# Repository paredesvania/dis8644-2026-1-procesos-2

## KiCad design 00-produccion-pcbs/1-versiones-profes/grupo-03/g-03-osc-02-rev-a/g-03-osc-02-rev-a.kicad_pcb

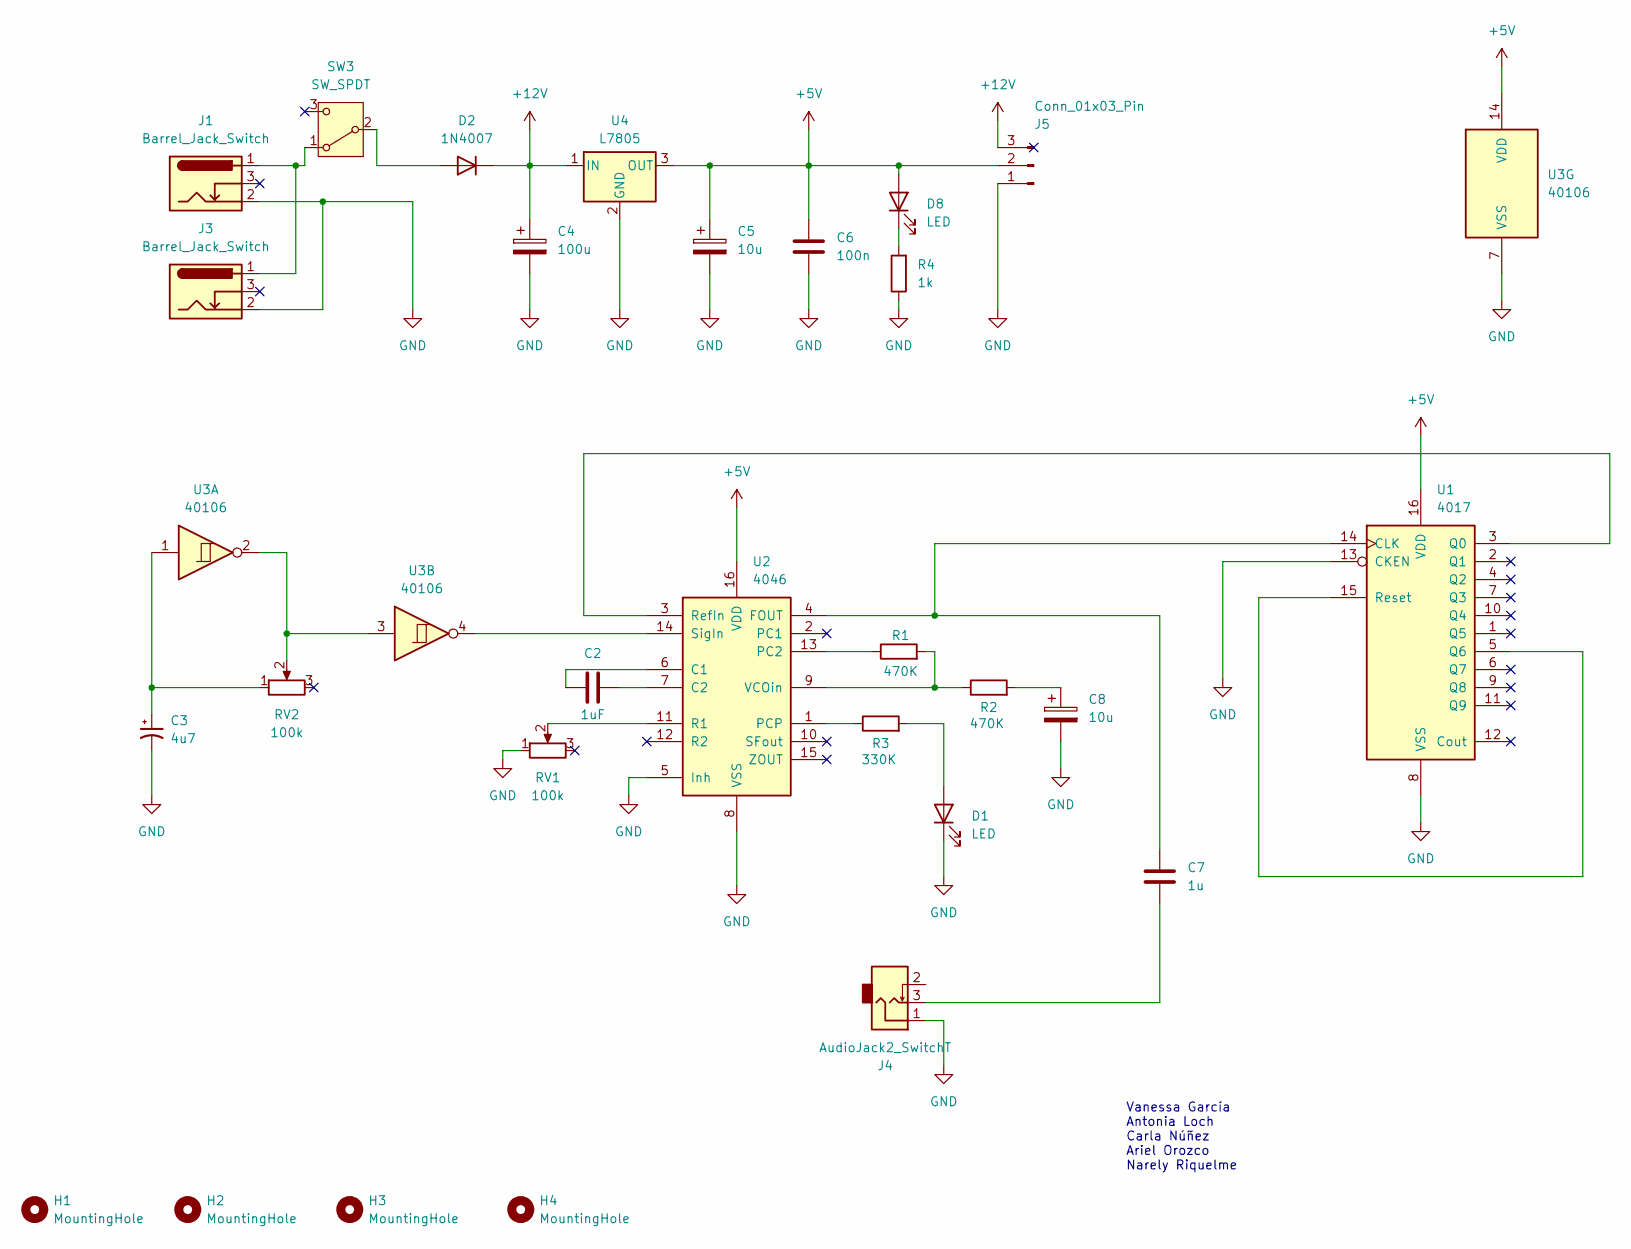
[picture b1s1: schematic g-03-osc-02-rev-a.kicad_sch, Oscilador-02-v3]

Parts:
C2: 1uF; CP_Radial_D5.0mm_P2.00mm
C3: 4u7; CP_Radial_D5.0mm_P2.00mm
C4: 100u; CP_Radial_D8.0mm_P3.80mm
C5, C8: 10u; CP_Radial_D4.0mm_P2.00mm
C6: 100n; C_Disc_D5.0mm_W2.5mm_P2.50mm
C7: 1u; C_Disc_D5.0mm_W2.5mm_P2.50mm
D1, D8: LED; LED_D5.0mm
D2: 1N4007; D_DO-41_SOD81_P10.16mm_Horizontal
H1, H2, H3, H4: MountingHole; MountingHole_3.2mm_M3
J1, J3: Barrel_Jack_Switch; BarrelJack_Horizontal
J4: AudioJack2_SwitchT; PJ301M-12
J5: Conn_01x03_Pin; PinSocket_1x03_P2.54mm_Vertical
R1, R2: 470K; R_Axial_DIN0207_L6.3mm_D2.5mm_P10.16mm_Horizontal
R3: 330K; R_Axial_DIN0207_L6.3mm_D2.5mm_P10.16mm_Horizontal
R4: 1k; R_Axial_DIN0207_L6.3mm_D2.5mm_P10.16mm_Horizontal
RV1, RV2: 100k; Potentiometer_Alps_RK163_Single_Horizontal
SW3: SW_SPDT; spdt_ssd12d00g3
U1: 4017; DIP-16_W7.62mm_LongPads
U2: 4046; DIP-16_W7.62mm_LongPads
U3: 40106; DIP-14_W7.62mm_LongPads
U4: L7805; TO-220-3_Horizontal_TabDown

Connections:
+5V: C5.1, C6.1, D8.2 (A), J5.2, U1.16 (VDD), U2.16 (VDD), U3.14 (VDD), U4.3 (OUT)
+12V: C4.1, D2.1 (K), J5.3, U4.1 (IN)
GND: C3.2, C4.2, C5.2, C6.2, C8.2, D1.1 (K), J1.2, J3.2, J4.1, J5.1, R4.1, RV1.1, U1.8 (VSS), U1.13 (CKEN), U2.5 (Inh), U2.8 (VSS), U3.7 (VSS), U4.2 (GND)
unnamed: C3.1, RV2.1, U3.1
unnamed: C7.2, J4.3
unnamed: C8.1, R2.2
unnamed: D1.2 (A), R3.2
unnamed: D2.2 (A), SW3.2 (B)
unnamed: D8.1 (K), R4.2
unnamed: RV2.2, U3.2, U3.3
unnamed: J1.1, J3.1, SW3.1 (A)
unnamed: C7.1, U1.14 (CLK), U2.4 (FOUT)
unnamed: U1.3 (Q0), U2.3 (RefIn)
unnamed: U1.5 (Q6), U1.15 (Reset)
unnamed: C2.1, U2.6 (C1)
unnamed: C2.2, U2.7 (C2)
unnamed: R1.1, U2.13 (PC2)
unnamed: R3.1, U2.1 (PCP)
unnamed: RV1.2, U2.11 (R1)
unnamed: U2.14 (SigIn), U3.4
unnamed: R1.2, R2.1, U2.9 (VCOin)

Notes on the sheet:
Vanessa García Antonia Loch Carla Núñez Ariel Orozco Narely Riquelme

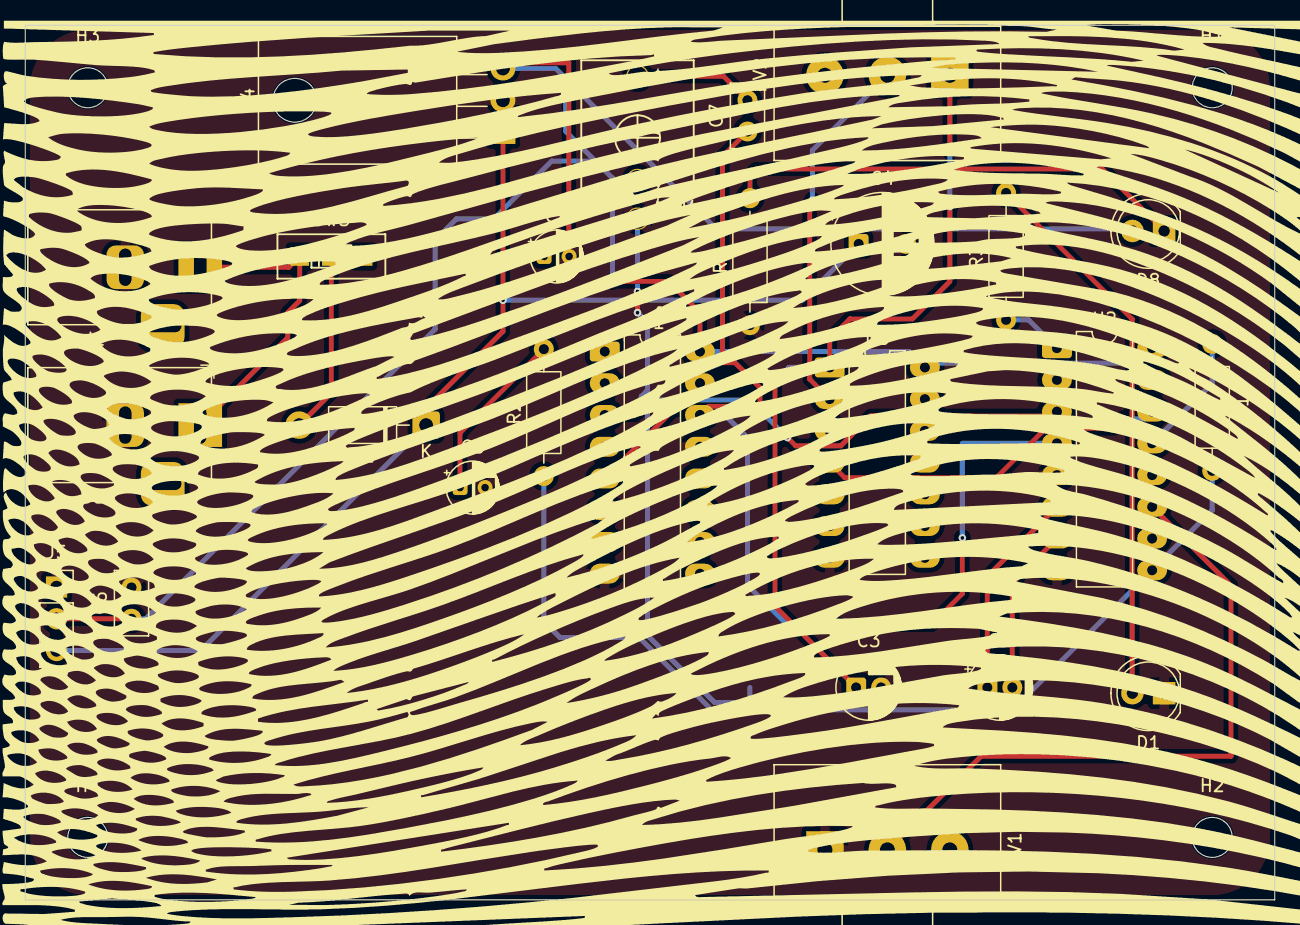
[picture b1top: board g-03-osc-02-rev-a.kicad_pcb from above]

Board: 2 copper layers, 100.0 x 70.0 mm, 29 parts (0 on the bottom side), 21 nets.

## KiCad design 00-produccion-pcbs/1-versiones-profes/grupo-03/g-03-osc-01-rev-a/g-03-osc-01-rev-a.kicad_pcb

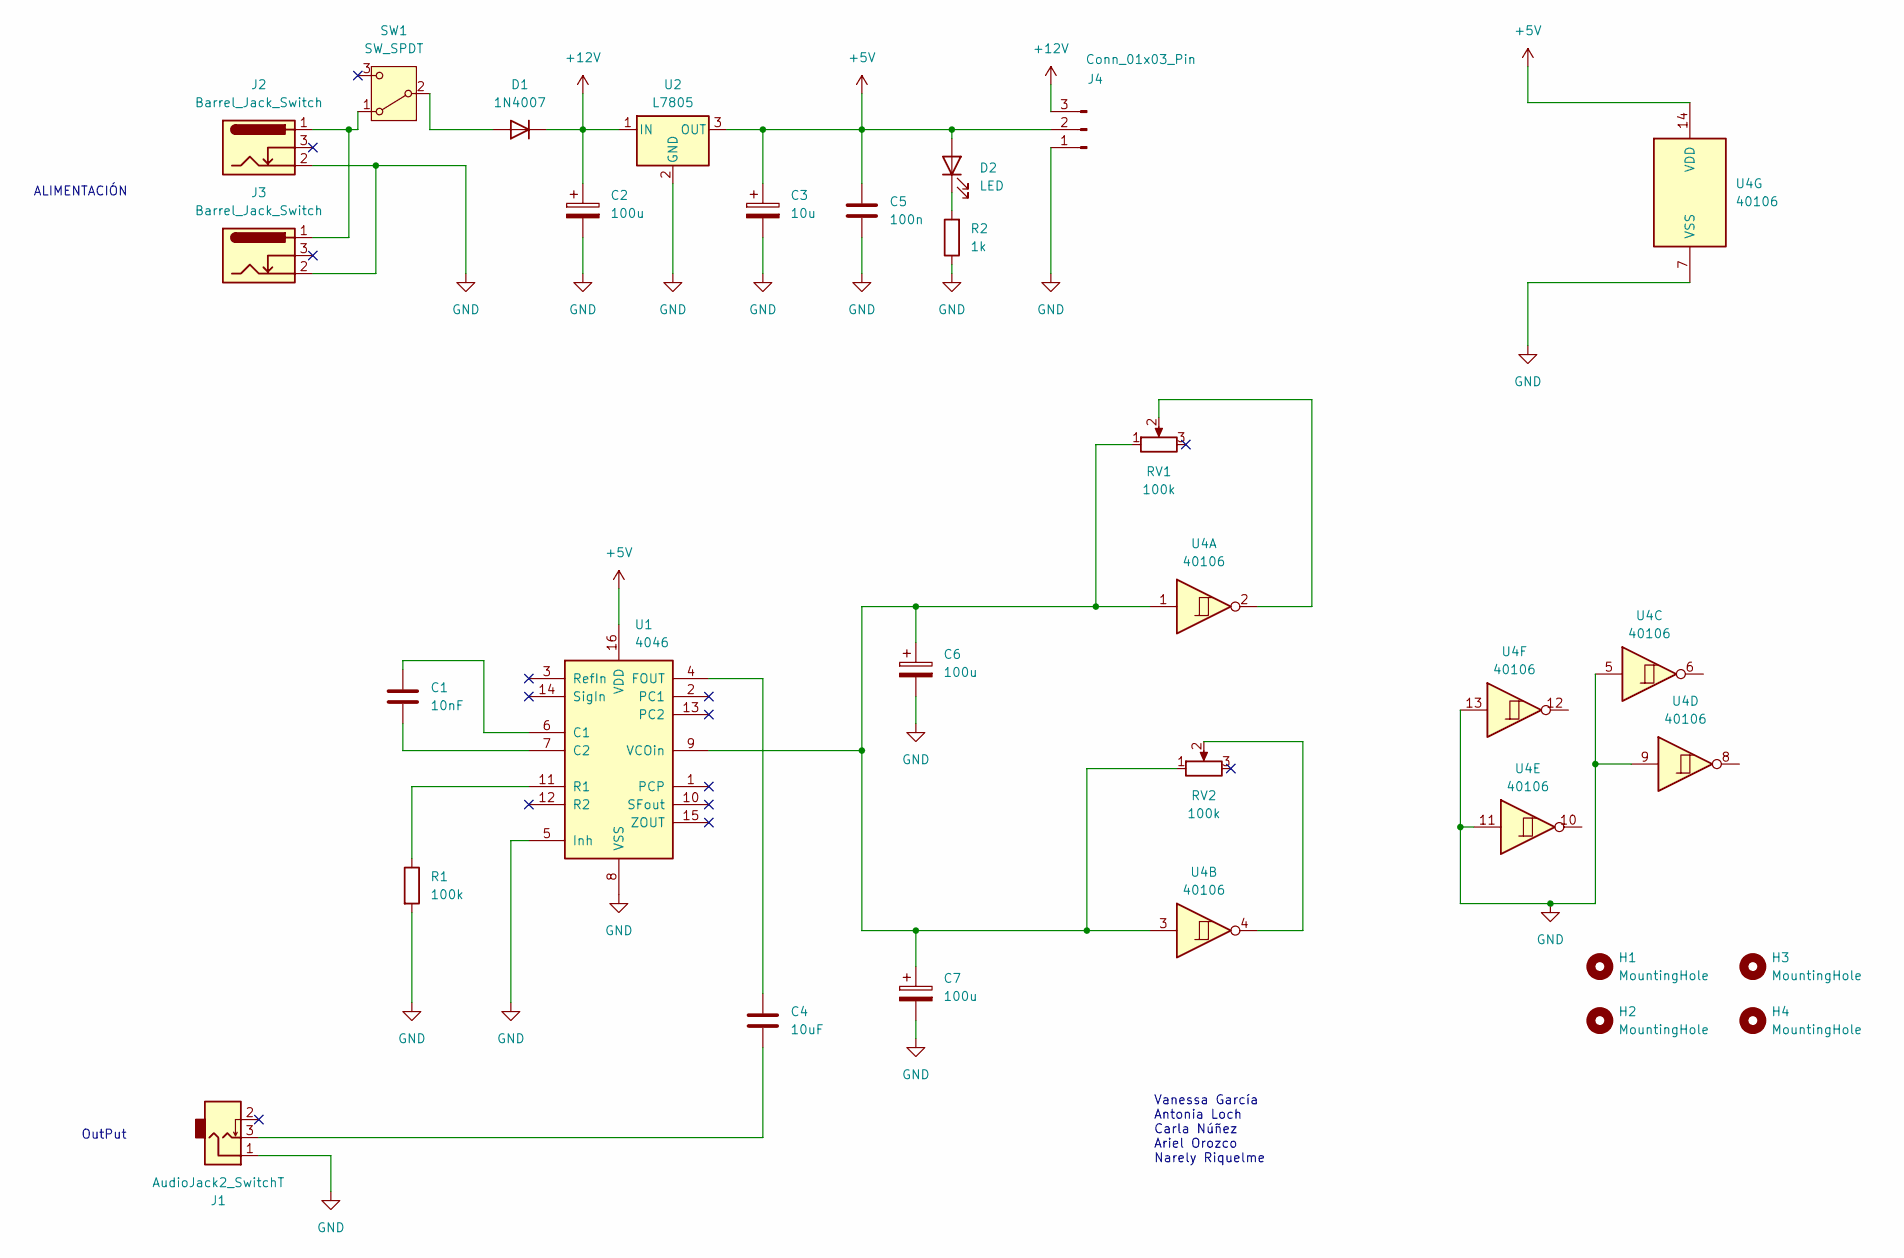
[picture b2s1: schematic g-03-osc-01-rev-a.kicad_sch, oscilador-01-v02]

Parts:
C1: 10nF; C_Disc_D3.8mm_W2.6mm_P2.50mm
C2, C6, C7: 100u; CP_Radial_D8.0mm_P3.80mm
C3: 10u; CP_Radial_D4.0mm_P2.00mm
C4: 10uF; CP_Radial_D5.0mm_P2.00mm
C5: 100n; C_Disc_D5.0mm_W2.5mm_P2.50mm
D1: 1N4007; D_DO-41_SOD81_P10.16mm_Horizontal
D2: LED; LED_D5.0mm
H1, H2, H3, H4: MountingHole; MountingHole_3.2mm_M3
J1: AudioJack2_SwitchT; PJ301M-12
J2, J3: Barrel_Jack_Switch; BarrelJack_Horizontal
J4: Conn_01x03_Pin; PinSocket_1x03_P2.54mm_Vertical
R1: 100k; R_Axial_DIN0207_L6.3mm_D2.5mm_P10.16mm_Horizontal
R2: 1k; R_Axial_DIN0207_L6.3mm_D2.5mm_P10.16mm_Horizontal
RV1, RV2: 100k; Potentiometer_Alps_RK163_Single_Horizontal
SW1: SW_SPDT; spdt_ssd12d00g3
U1: 4046; DIP-16_W7.62mm_LongPads
U2: L7805; TO-220-3_Horizontal_TabDown
U4: 40106

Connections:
+5V: C3.1, C5.1, D2.2 (A), J4.2, U1.16 (VDD), U2.3 (OUT), U4.14 (VDD)
+12V: C2.1, D1.1 (K), J4.3, U2.1 (IN)
GND: C2.2, C3.2, C5.2, C6.2, C7.2, J1.1, J2.2, J3.2, J4.1, R1.2, R2.1, U1.5 (Inh), U1.8 (VSS), U2.2 (GND), U4.5, U4.7 (VSS), U4.9, U4.11, U4.13
unnamed: C4.2, J1.3
unnamed: D1.2 (A), SW1.2 (B)
unnamed: D2.1 (K), R2.2
unnamed: RV1.2, U4.2
unnamed: RV2.2, U4.4
unnamed: J2.1, J3.1, SW1.1 (A)
unnamed: C1.2, U1.6 (C1)
unnamed: C1.1, U1.7 (C2)
unnamed: C4.1, U1.4 (FOUT)
unnamed: R1.1, U1.11 (R1)
unnamed: C6.1, C7.1, RV1.1, RV2.1, U1.9 (VCOin), U4.1, U4.3

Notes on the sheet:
ALIMENTACIÓN
OutPut
Vanessa García Antonia Loch Carla Núñez Ariel Orozco Narely Riquelme

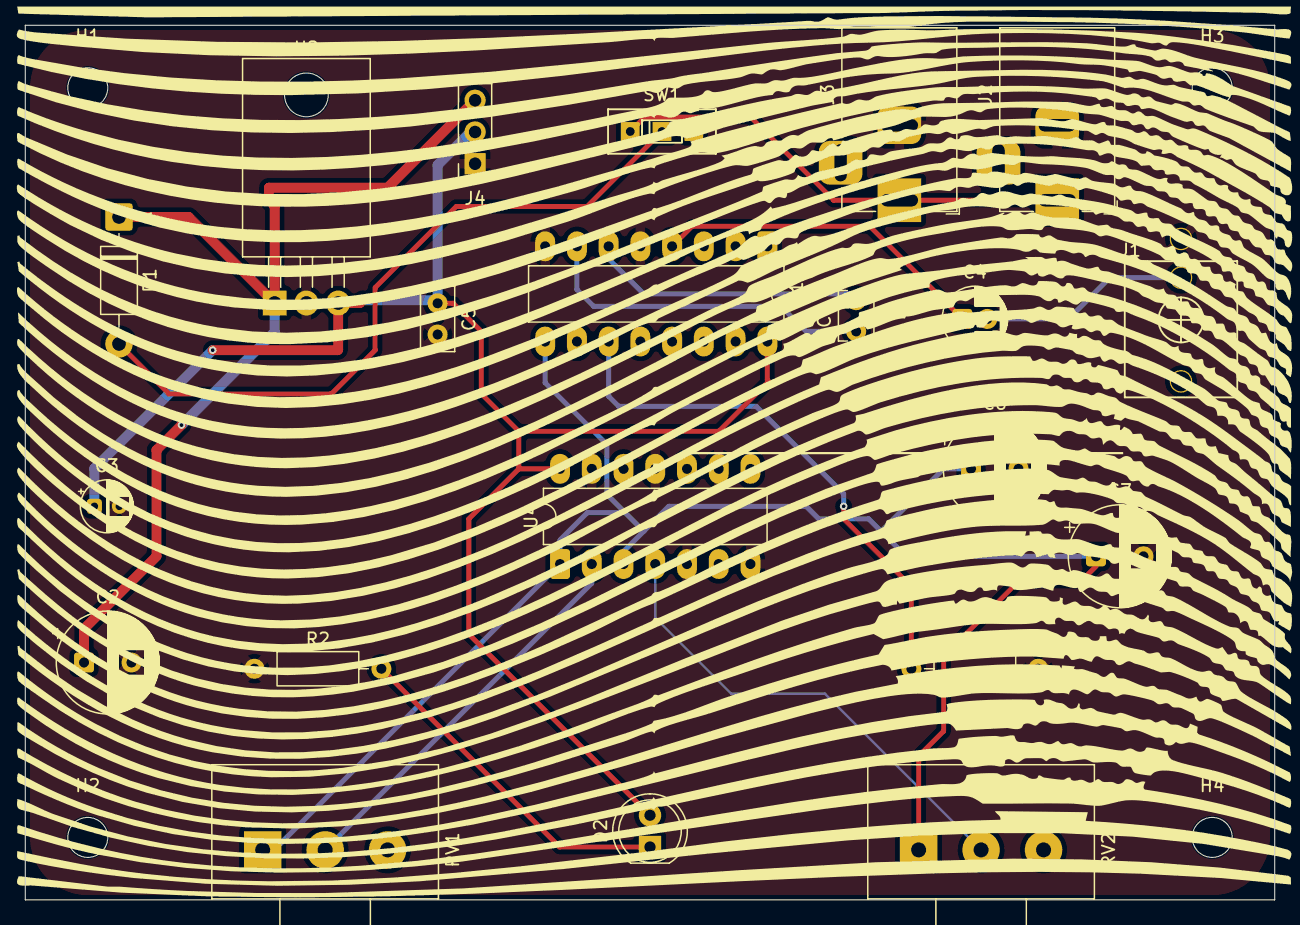
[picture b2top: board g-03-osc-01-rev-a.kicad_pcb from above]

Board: 2 copper layers, 100.0 x 70.0 mm, 25 parts (0 on the bottom side), 14 nets.

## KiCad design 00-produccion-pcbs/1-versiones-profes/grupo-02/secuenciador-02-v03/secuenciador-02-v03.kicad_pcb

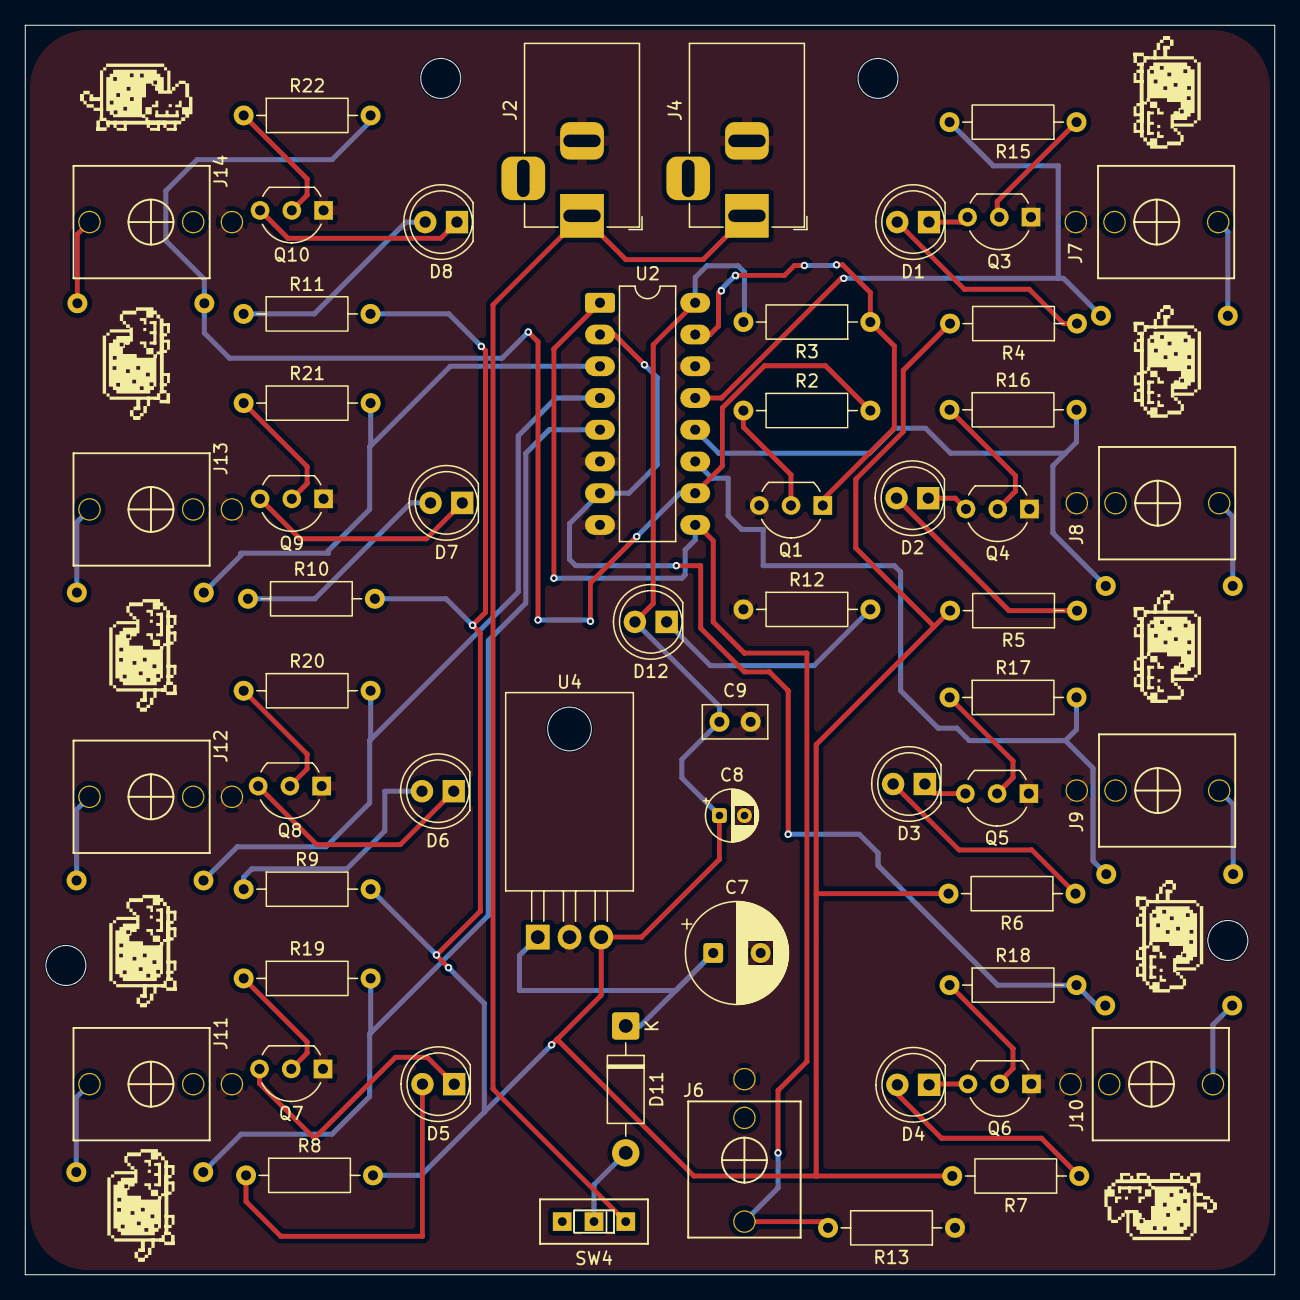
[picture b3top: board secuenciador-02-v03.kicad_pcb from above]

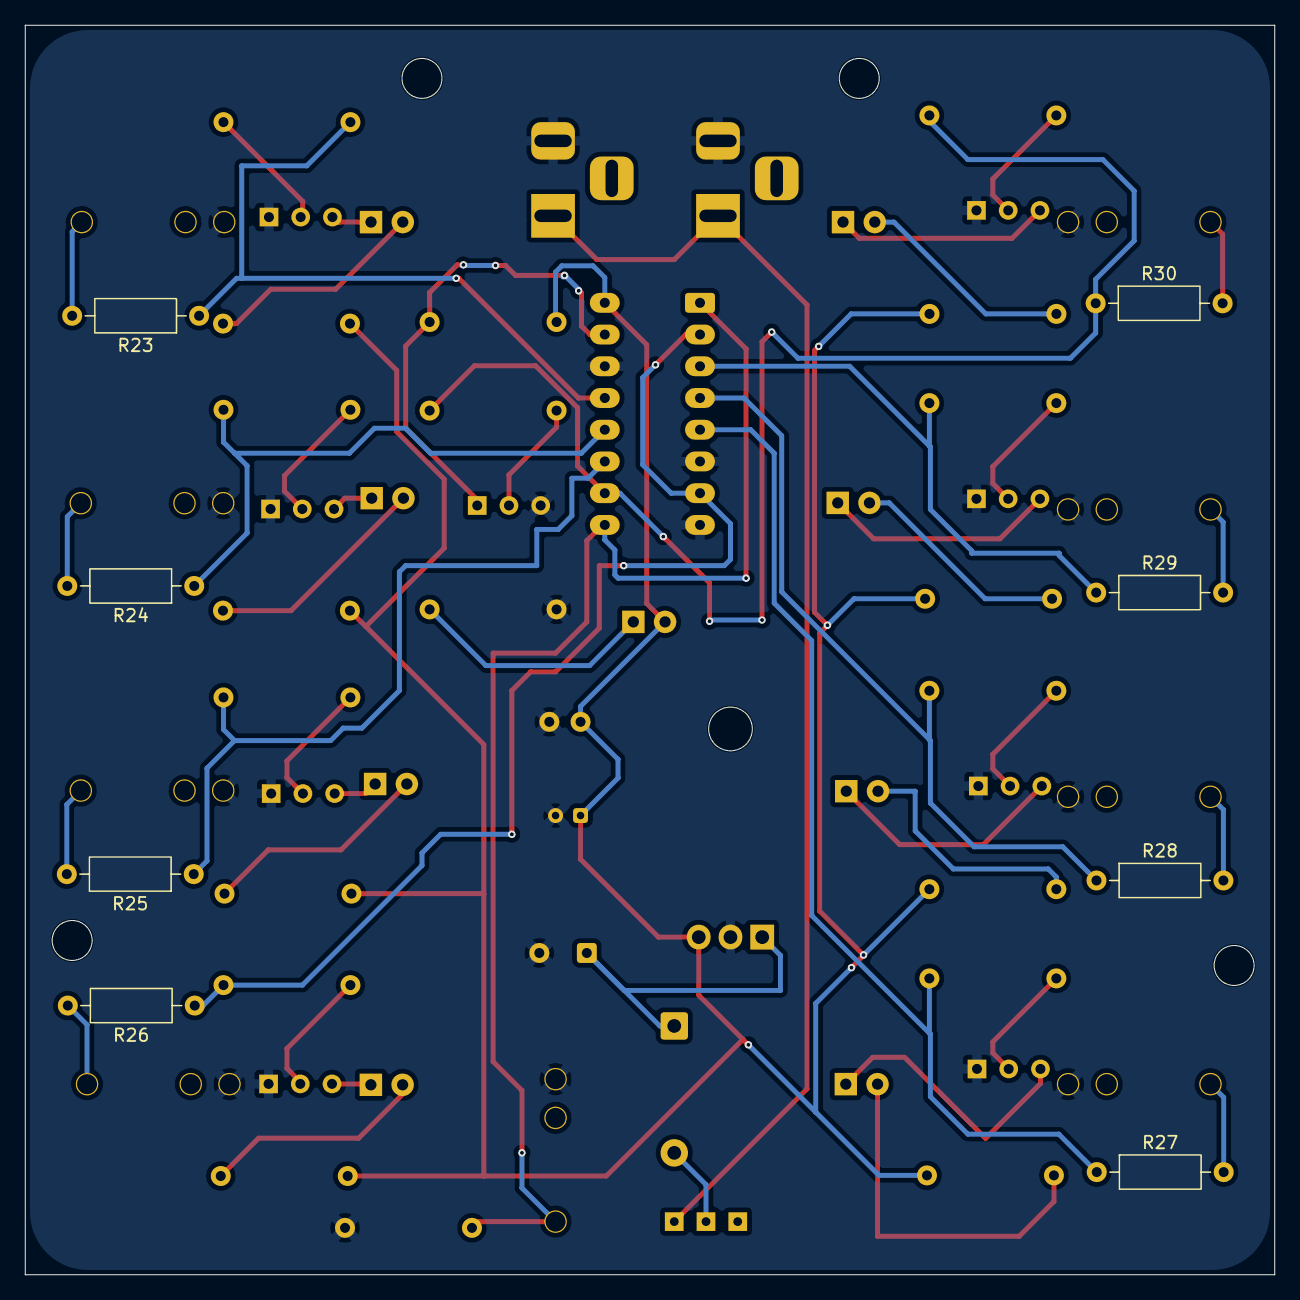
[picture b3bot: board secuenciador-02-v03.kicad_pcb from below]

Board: 2 copper layers, 100.0 x 100.0 mm, 68 parts (8 on the bottom side), 49 nets.

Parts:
C7: 100u; CP_Radial_D8.0mm_P3.80mm
C8: 10u; CP_Radial_D4.0mm_P2.00mm
C9: 100n; C_Disc_D5.0mm_W2.5mm_P2.50mm
D1, D2, D3, D4, D5, D6, D7, D8, D12: LED; LED_D5.0mm
D11: 1N4007; D_DO-41_SOD81_P10.16mm_Horizontal
H1, H2, H3, H4: M3; MountingHole_3.2mm_M3
J2, J4: Barrel_Jack_Switch; BarrelJack_Horizontal
J6, J7, J8, J9, J10, J11, J12, J13, J14: AudioJack2_SwitchT; PJ301M-12
Q1: BC548; TO-92_Inline_Wide
Q3, Q4, Q5, Q6, Q7, Q8, Q9, Q10: PN2222A; TO-92_Inline_Wide
R2: 10k; R_Axial_DIN0207_L6.3mm_D2.5mm_P10.16mm_Horizontal
R3, R12, R15, R16, R17, R18, R19, R20, R21, R22, R23, R24, R25, R26, R27, R28, R29, R30: 1k; R_Axial_DIN0207_L6.3mm_D2.5mm_P10.16mm_Horizontal
R4, R5, R6, R7, R8, R9, R10, R11: 220; R_Axial_DIN0207_L6.3mm_D2.5mm_P10.16mm_Horizontal
R13: 100k; R_Axial_DIN0207_L6.3mm_D2.5mm_P10.16mm_Horizontal
SW4: SW_SPDT; spdt_ssd12d00g3
U2: 4015; DIP-16_W7.62mm_LongPads
U4: L7805; TO-220-3_Horizontal_TabDown

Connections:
+5V: C8.1, C9.1, D12.2 (A), R3.2, R4.2, R5.2, R6.2, R7.2, R8.2, R9.2, R10.2, R11.2, U2.16 (Vdd), U4.3 (OUT)
+12V: C7.1, D11.1 (K), U4.1 (IN)
GND: C7.2, C8.2, C9.2, J2.2, J4.2, J6.1, J7.1, J8.1, J9.1, J10.1, J11.1, J12.1, J13.1, J14.1, Q1.3 (E), Q3.1 (E), Q4.1 (E), Q5.1 (E), Q6.1 (E), Q7.1 (E), Q8.1 (E), Q9.1 (E), Q10.1 (E), R12.1, R13.1, U2.6 (MR), U2.8 (Vss), U2.14 (MR), U4.2 (GND)
unnamed: D1.2 (A), R4.1
unnamed: D1.1 (K), Q3.3 (C)
unnamed: D2.2 (A), R5.1
unnamed: D2.1 (K), Q4.3 (C)
unnamed: D3.2 (A), R6.1
unnamed: D3.1 (K), Q5.3 (C)
unnamed: D4.2 (A), R7.1
unnamed: D4.1 (K), Q6.3 (C)
unnamed: D5.2 (A), R8.1
unnamed: D5.1 (K), Q7.3 (C)
unnamed: D6.2 (A), R9.1
unnamed: D6.1 (K), Q8.3 (C)
unnamed: D7.2 (A), R10.1
unnamed: D7.1 (K), Q9.3 (C)
unnamed: D8.2 (A), R11.1
unnamed: D8.1 (K), Q10.3 (C)
unnamed: D11.2 (A), SW4.2 (B)
unnamed: D12.1 (K), R12.2
unnamed: J7.3, R23.2
unnamed: J8.3, R24.2
unnamed: J9.3, R25.2
unnamed: J10.3, R26.2
unnamed: J11.3, R27.2
unnamed: J12.3, R28.2
unnamed: J13.3, R29.2
unnamed: J14.3, R30.2
unnamed: Q1.2 (B), R2.1
unnamed: Q1.1 (C), R3.1, U2.15 (D)
unnamed: Q3.2 (B), R15.1
unnamed: Q4.2 (B), R16.1
unnamed: Q5.2 (B), R17.1
unnamed: Q6.2 (B), R18.1
unnamed: Q7.2 (B), R19.1
unnamed: Q8.2 (B), R20.1
unnamed: Q9.2 (B), R21.1
unnamed: Q10.2 (B), R22.1
unnamed: J2.1, J4.1, SW4.1 (A)
unnamed: J6.3, R13.2, U2.1 (CP), U2.9 (CP)
unnamed: R18.2, R26.1, U2.2 (Q4), U2.7 (D)
unnamed: R19.2, R27.1, U2.5 (Q1)
unnamed: R20.2, R28.1, U2.4 (Q2)
unnamed: R21.2, R29.1, U2.3 (Q3)
unnamed: R2.2, R22.2, R30.1, U2.10 (Q4)
unnamed: R15.2, R23.1, U2.13 (Q1)
unnamed: R16.2, R24.1, U2.12 (Q2)
unnamed: R17.2, R25.1, U2.11 (Q3)

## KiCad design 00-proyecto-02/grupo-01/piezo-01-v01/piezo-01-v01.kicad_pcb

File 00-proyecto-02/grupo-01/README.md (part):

# proyecto-02

## Grupo

Número de grupo: 01

Tema del grupo: Piezo

Integrantes:

- Benjamín Alonso Álvarez Pavez / [benjaminalvarez21](<https://github.com/disenoUDP/dis8644-2026-1-procesos-2/tree/main/03-benjaminalvarez21>)
- Anays Valentina Cornejo Candia / [Anaysval](<https://github.com/disenoUDP/dis8644-2026-1-procesos-2/tree/main/09-Anaysval>)
- Bruno Ferrari Meyer / [chknngttts](<https://github.com/disenoUDP/dis8644-2026-1-procesos-2/tree/main/11-chknngttts>)
- Lucas Ignacio Ortiz Aguirre / [ryukivol](<https://github.com/disenoUDP/dis8644-2026-1-procesos-2/tree/main/21-ryukivol>)
- Nicolás Elías Valdés Greve / [nicolasvaldesgreve](<https://github.com/disenoUDP/dis8644-2026-1-procesos-2/tree/main/31-nicolasvaldesgreve>)

## Circuito 1

maincra

### Descripción general/conceptual 1

Este módulo te permite interactuar con el sintetizador mediante vibraciones en el piezo, tales como golpes en la misma superficie en la que se encuentra el componente o utilizándolo en nuestro cuerpo y causar vibraciones con nuestra garganta. Estas vibraciones serás captadas por el piezo, lo cual lo tomará como señal para avanzar en el secuenciador.

### Descripción de funcionamiento 1

El circuito se conforma de 7 partes:
  - Piezoeléctrico
  - Pre-Amp (TL072)
  - Inversor de señal (2N2222)
  - Regulador de voltaje (L7805CV)
  - Filtro Low-pass
  - Clock (NE555P)
  - Secuenciador (CD4017)

Como estándar en el trabajo todos tenemos que alimentar nuestro circuito con 5V. Para esto usamos el L7805CV

El piezo tiene 3 estados al recibir señal. ( imagen explicativa )

Para que el Pre-Amp pueda recibir la señal correctamente se necesita crear un voltaje medio entre VCC y GND. Para esto se usan 2 Resistencias del mismo valor, que dividen el voltaje a la mitad **``5V ---> 2.5V``**, esto permite que capte la señal completa y funcione correctamente. El Pre-Amp en nuestro caso también funciona para aumentar la sensibilidad del piezo, normalmente este solo detecta las señales directas al disco cerámico del piezo, pero con el Pre-Amp logramos que detecte señales a varios centímetros de este. 

Para afinar la señal que recibe el inversor, colocamos un filtro low-pass, esto permite que solo corriente bajo los 500hz *aprox.* avancen en el circuito. Esta señal entra al transistor (2N2222) que invierte la señal que recibe, puesto que el Clock (NE555P) busca recibir señales negativas en su pin 2 (Trigger) para funcionar. El Clock en modo monoestable se conecta con el pin 14 del secuenciador (CD4017) para que señale cuando se avanza en los steps. 

### Descubrimientos

- Modificando los valores de las resistencias, se logra amplificar la sensibilidad del piezo (gracias misaaaaaa).
- Tener protoboard con los orificios **no** suelto es vital para que el circuito sea estable y se pueda mover.
- Que ciertos amplificadores tienen usos específicos, como el LM386 que es óptimo para parlantes, pero no piezos.
- Se pueden sustituir componentes con valores diferentes **``2.2k Ω ---> 47 Ω``**

### Esquemático 

### PCB 1

### Documentación audiovisual funcionamiento protoboard 1

Incluir enlace a video en youtube (puede estar en Oculto) con protoboard funcionando

### BOM

| Componente | Cantidad | Valor unitario | Link |
| --- | --- | --- | --- |
| Chip NE555P | 1 | $490 | <https://www.victronics.cl/circuitos-integrados/lm555cngeneralpurposebipolartimerdip8/> |
| Chip TL072CP | 1 | $990 | <https://www.victronics.cl/circuitos-integrados/tl072cpdualjfetlowpoweropamplifierdip8/> |
| Chip CD4017 | 1 | $890 | <https://www.mechatronicstore.cl/circuito-integrado-4017-contador/?srsltid=AfmBOopG29clQvJ0CqcNNp17wxEDjZ1w8dAWqRPMAcTqycciqYjHE40h>
| Regulador L7805CV | 1 | $350 | <https://www.victronics.cl/reguladores/reguladorvoltl7805cv5v-15ato220/> |
| Diodo 1N4007 | 1 | $200 | <https://www.mechatronicstore.cl/diodo-rectificador-in4007-1n4007-4007/> |
| Diodo BAT85 | 2 | $586 | <https://cl.rsdelivers.com/product/nexperia/bat85113/nexperia-diodo-bat85113-diodo-schottky-200-ma-30-v/0300978> |
| Transistor 2N2222 | 1 | $200 | <https://www.mechatronicstore.cl/transistor-2n2222/> |
| Potenciómetro B10K | 1 | $495 | <https://altronics.cl/potenciometro-lineal-10k-b10k> |
| Potenciómetro B500K | 1 | $495 | <https://altronics.cl/potenciometro-lineal-500k-b500k?search=b500k> |
| LED 3mm | 5 | $100 | <https://www.mechatronicstore.cl/led-3mm-5mm/> |
| Resistencia 47 Ω | 1 | $90 | <https://www.electroardu.cl/resistencias-1k-ohm?srsltid=AfmBOor81HKrzfoOTnLK3FU6ObPuf1EPUVMS0naCwqMNIzGt8LYDiUYt> |
| Resistencia 100 Ω | 1 | $90 | <https://www.electroardu.cl/resistencias-1k-ohm?srsltid=AfmBOor81HKrzfoOTnLK3FU6ObPuf1EPUVMS0naCwqMNIzGt8LYDiUYt> |
| Resistencia 220 Ω | 1 | $90 | <https://www.electroardu.cl/resistencias-1k-ohm?srsltid=AfmBOor81HKrzfoOTnLK3FU6ObPuf1EPUVMS0naCwqMNIzGt8LYDiUYt> |
| Resistencia 1 KΩ | 8 | $90 | <https://www.electroardu.cl/resistencias-1k-ohm?srsltid=AfmBOor81HKrzfoOTnLK3FU6ObPuf1EPUVMS0naCwqMNIzGt8LYDiUYt> |
| Resistencia 10 KΩ | 4 | $90 | <https://www.electroardu.cl/resistencias-1k-ohm?srsltid=AfmBOor81HKrzfoOTnLK3FU6ObPuf1EPUVMS0naCwqMNIzGt8LYDiUYt> |
| Resistencia 100 KΩ | 5 | $90 | <https://www.electroardu.cl/resistencias-1k-ohm?srsltid=AfmBOor81HKrzfoOTnLK3FU6ObPuf1EPUVMS0naCwqMNIzGt8LYDiUYt> |
| Condensador cerámico 4.7 nF | 1 | $100 | <https://www.mechatronicstore.cl/condensadores-ceramicos-distintos-valores/> |
| Condensador cerámico 10 nF | 1 | $100 | <https://www.mechatronicstore.cl/condensadores-ceramicos-distintos-valores/> |
| Condensador cerámico 100 nF | 4 | $100 | <https://www.mechatronicstore.cl/condensadores-ceramicos-distintos-valores/> |
| Condensador polarizado 10 µF | 2 | $100 | <https://www.mechatronicstore.cl/condensador-capacitorio-de-electrolitico-por-unidad-varios-valores/> |
| Condensador polarizado 100 µF | 3 | $100 | <https://www.mechatronicstore.cl/condensador-capacitorio-de-electrolitico-por-unidad-varios-valores/> | 
| Cables dupont 40 uni. | 1 | $2.990 | <https://mcielectronics.cl/shop/product/cable-dupont-macho-macho-20cm-pack-40-unidades-2/> |
| Cables caimán | 2 | $1.990 | <https://www.mechatronicstore.cl/cable-conector-cocodrilo-o-caiman-5-unidades/> |
| Batería 9V recargable | 1 | $7.990 | <https://www.sodimac.cl/sodimac-cl/articulo/110251085/bateria-recargable-9v/110251089> |
| Conector batería | 1 | $1.990 | <https://mcielectronics.cl/shop/product/conector-para-baterias-de-9v-9800/?srsltid=AfmBOorf4iqHmZZbBCSLCPoI-UFTBMuBMtXEwLw-ia48KteW5jir8sIx> |
| Piezo | 1 | $990 | <https://www.mechatronicstore.cl/sensor-piezoelectrico-27mm-con-cable/> |
| Interruptor Switch | 1 | $570 | <https://www.katode.cl/switches/1339-interruptor-switch-2-pines-on-off-corto.html?srsltid=AfmBOorJlIeUySzAORFwXSattHKE4BKH2LmhhXZS_8fZ4MW-G6kwnxqA> |

## Circuito 2

Budumtz

### Descripción general/conceptual 2

Este módulo, al igual que el anterior, permite que uno pueda interactuar con el sintetizador al que esté conectado el piezo, pero en este caso se necesita contacto directo al componente lo cual permitirá que lo que esté conectado a este se active.

### Descripción de funcionamiento 2

El circuito se conforma por 4 partes:

+ Piezoeléctrico
+ High pass filter
+ Op-Amp (LM324)
+ Inversor de señal (2N2222)
+ Regulador de voltaje (L7805CV)

Este circuito emplea el funcionamiento de *activador* es decir, envía señal a un módulo siguiente, el cual para verificar su funcionamiento se utiliza un led o se puede conectar a una salida de audio utilizando un Amp y parlante. 

El chip LM324 se utiliza como DC offset, regulando el voltaje bajando a la mitad 9V ---> 4.5V. Además, cuenta con una salida de audio [pin 7] que utilizamos como salida para el siguiente módulo. De esta manera al interactuar con el piezo la señal se ve distorsionada por un breve periodo de tiempo ya que la señal que emite el circuito es constante.

En cuanto a los reguladores de voltaje, ya que nuestro chip LM324 cuenta con uno decidimos crear dos versiones, una con el estándar dado para la sección y uno con el integrado en el circuito.

Por otro lado, tuvimos un problema relacionado con la PCB, al ejecutar DRC da error: conexión de alivio térmico a zona incompleta al [pin 11] con el GND, problema que intentamos solucionar, pero no hubo éxito.

Archivo piezo-02-v03: Con regulador estándar.

Archivo piezo-02-v04: Solo regulador integrado.

### Esquemático 2

### PCB 2

```markdown

```

```markdown

```

### Documentación audiovisual funcionamiento protoboard 2

Incluir enlace a video en youtube (puede estar en Oculto) con protoboard funcionando

### BOM

| Componente | Cantidad | Valor unitario | Link |
| --- | --- | --- | --- |
| Chip LM324 | 1 | $590 | <https://www.mechatronicstore.cl/amplificador-operacional-lm324/?srsltid=AfmBOopyXPPvl24e9VRGUKZwKS9_gIp9S3hdacmTDOWF4O2ur2TF77QZ> |
| Potenciómetro B500K | 1 | $495 | <https://altronics.cl/potenciometro-lineal-500k-b500k?search=b500k> |
| LED 3mm | 1 | $100 | <https://www.mechatronicstore.cl/led-3mm-5mm/> |
| Transistor 2N2222 | 1 | $200 | <https://www.mechatronicstore.cl/transistor-2n2222/> |
| Resistencia 1 KΩ | 3| $90 | <https://www.electroardu.cl/resistencias-1k-ohm?srsltid=AfmBOor81HKrzfoOTnLK3FU6ObPuf1EPUVMS0naCwqMNIzGt8LYDiUYt> |
| Resistencia 10 KΩ | 1 | $90 | <https://www.electroardu.cl/resistencias-1k-ohm?srsltid=AfmBOor81HKrzfoOTnLK3FU6ObPuf1EPUVMS0naCwqMNIzGt8LYDiUYt> |
| Resistencia 22K KΩ | 1 | $90 | <https://www.electroardu.cl/resistencias-1k-ohm?srsltid=AfmBOor81HKrzfoOTnLK3FU6ObPuf1EPUVMS0naCwqMNIzGt8LYDiUYt> |
| Resistencia 100 KΩ | 3 | $90 | <https://www.electroardu.cl/resistencias-1k-ohm?srsltid=AfmBOor81HKrzfoOTnLK3FU6ObPuf1EPUVMS0naCwqMNIzGt8LYDiUYt> |
| Resistencia 1 MΩ | 3 | $90 | <https://www.electroardu.cl/resistencias-1k-ohm?srsltid=AfmBOor81HKrzfoOTnLK3FU6ObPuf1EPUVMS0naCwqMNIzGt8LYDiUYt> |
| Condensador cerámico 4.7 nF | 1 | $100 | <https://www.mechatronicstore.cl/condensadores-ceramicos-distintos-valores/> |
| Condensador cerámico 100 nF | 2 | $100 | <https://www.mechatronicstore.cl/condensadores-ceramicos-distintos-valores/> |
| Condensador polarizado 10 µF | 2 | $100 | <https://www.mechatronicstore.cl/condensador-capacitorio-de-electrolitico-por-unidad-varios-valores/>|
| Condensador polarizado 100 µF | 2 | $100 | <https://www.mechatronicstore.cl/condensador-capacitorio-de-electrolitico-por-unidad-varios-valores/> | 
| Cables dupont 40 uni. | 1 | $2.990 | <https://mcielectronics.cl/shop/product/cable-dupont-macho-macho-20cm-pack-40-unidades-2/> |
| Cables caimán | 2 | $1.990 | <https://www.mechatronicstore.cl/cable-conector-cocodrilo-o-caiman-5-unidades/> |
| Batería 9V recargable | 1 | $7.990 | <https://www.sodimac.cl/sodimac-cl/articulo/110251085/bateria-recargable-9v/110251089> |
| Conector batería | 1 | $1.990 | <https://mcielectronics.cl/shop/product/conector-para-baterias-de-9v-9800/?srsltid=AfmBOorf4iqHmZZbBCSLCPoI-UFTBMuBMtXEwLw-ia48KteW5jir8sIx> |
| Piezo | 1 | $990 | <https://www.mechatronicstore.cl/sensor-piezoelectrico-27mm-con-cable/> |
| Interruptor Switch | 1 | $570 | <https://www.katode.cl/switches/1339-interruptor-switch-2-pines-on-off-corto.html?srsltid=AfmBOorJlIeUySzAORFwXSattHKE4BKH2LmhhXZS_8fZ4MW-G6kwnxqA> |

## Otros circuitos

En el piezo 01 usamos el HiFi Pre-Amp Circuit de [jevron1984](https://electronics.stackexchange.com/questions/348898/need-some-help-building-a-tl072-preamp-circuit). No era compatible con el circuito, después armamos un circuito propio utilizando el 2N2222, pero tampoco funcionó, por lo que lo sustituimos por el Pre-Amp de [PimPom](https://www.diyaudio.com/community/threads/tl072-as-mike-input-preamp.317907/).

En el piezo 02 armamos un Amp con el LM386, siguiendo el mismo esquemático que se nos entregó por misaaaaaa en el proyecto-01.

## Colaboración con otros grupos

### ¿Cómo ayudé a otro grupo?

+ Ayudamos al grupo 03 (osciladores 1) prestándoles dos potenciómetros B100K.
+ Ayudamos al grupo 03 (osciladores 1) con el comando para añadir imágenes en el README.md.
+ Ayudamos al grupo 03 (osciladores 1) con la gráfica de la PCB.
+ Ayudamos al grupo 06 (percutores) prestándoles la batería.
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
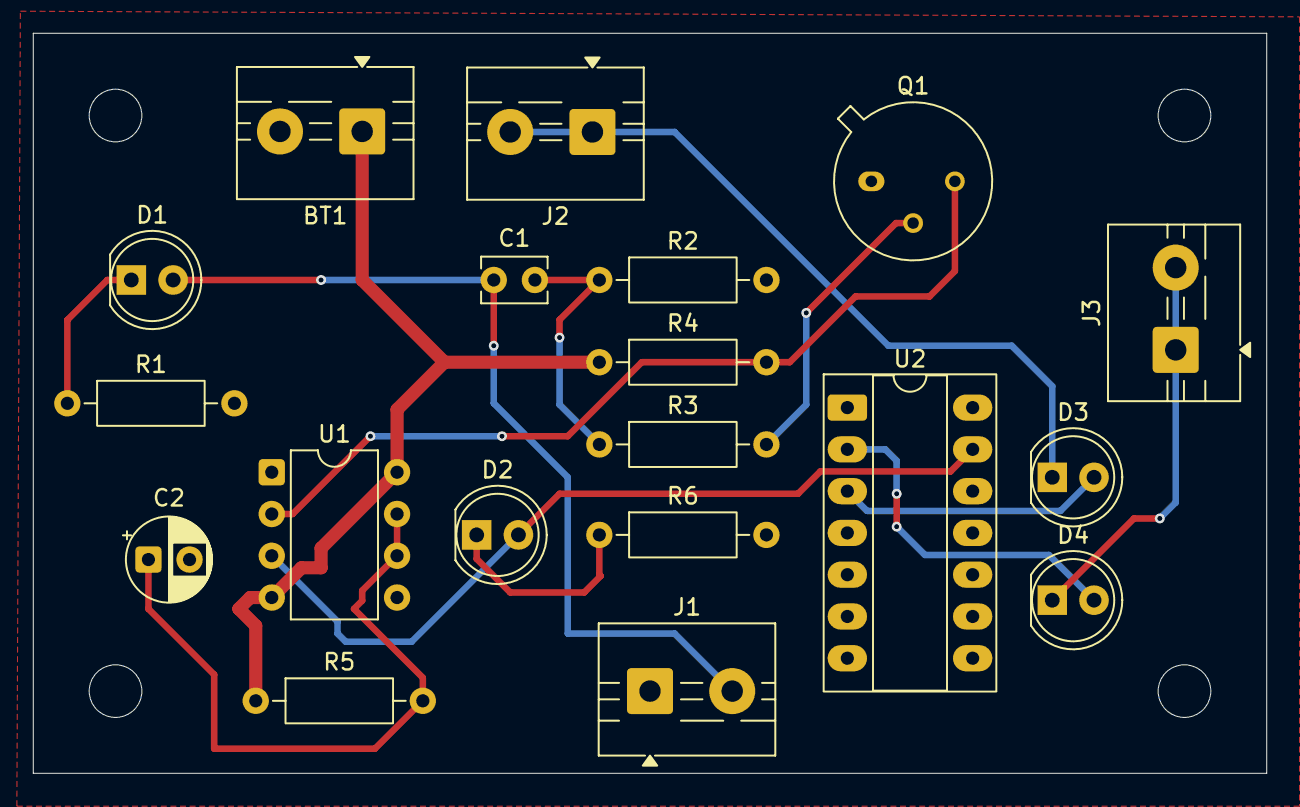
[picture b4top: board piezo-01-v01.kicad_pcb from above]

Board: 2 copper layers, 75.0 x 45.0 mm, 23 parts (0 on the bottom side), 14 nets.

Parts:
BT1: 5v; TerminalBlock_MaiXu_MX126-5.0-02P_1x02_P5.00mm
C1: 100n; C_Disc_D3.8mm_W2.6mm_P2.50mm
C2: 10 uF; CP_Radial_D5.0mm_P2.50mm
D1, D2, D3, D4: LED; LED_D5.0mm
H1, H2, H3, H4: MountingHole; MountingHole_3.2mm_M3
J1, J2, J3: Screw_Terminal_01x02; TerminalBlock_MaiXu_MX126-5.0-02P_1x02_P5.00mm
Q1: 2N2222; TO-39-3
R1, R3, R6: 1k; R_Axial_DIN0207_L6.3mm_D2.5mm_P10.16mm_Horizontal
R2: 100k; R_Axial_DIN0207_L6.3mm_D2.5mm_P10.16mm_Horizontal
R4: 1ok; R_Axial_DIN0207_L6.3mm_D2.5mm_P10.16mm_Horizontal
R5: 10k; R_Axial_DIN0207_L6.3mm_D2.5mm_P10.16mm_Horizontal
U1: NE555P; DIP-8_W7.62mm
U2: 4017; CERDIP-14_W7.62mm_SideBrazed_LongPads_Socket

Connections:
GND: BT1.2 (-), C2.2, J1.1, Q1.1 (E), R1.2, R2.2, R6.2, U1.1 (GND), U1.5 (CONT), U2.8 (VSS)
unnamed: C1.2, R2.1, R3.1
unnamed: C1.1, D1.2 (A), J1.2
unnamed: D1.1 (K), R1.1
unnamed: D2.2 (A), U1.3 (OUT), U2.13 (CKEN)
unnamed: D2.1 (K), R6.1
unnamed: D3.2 (A), U2.3 (Q0)
unnamed: D3.1 (K), J2.1, J2.2
unnamed: D4.2 (A), U2.2 (Q1)
unnamed: D4.1 (K), J3.1, J3.2
unnamed: Q1.2 (B), R3.2
unnamed: Q1.3 (C), R4.2, U1.2 (TRIG)
unnamed: C2.1, R5.2, U1.6 (THRES), U1.7 (DISCH)
VCC: BT1.1 (+), R4.1, R5.1, U1.4 (~RST), U1.8 (VCC)

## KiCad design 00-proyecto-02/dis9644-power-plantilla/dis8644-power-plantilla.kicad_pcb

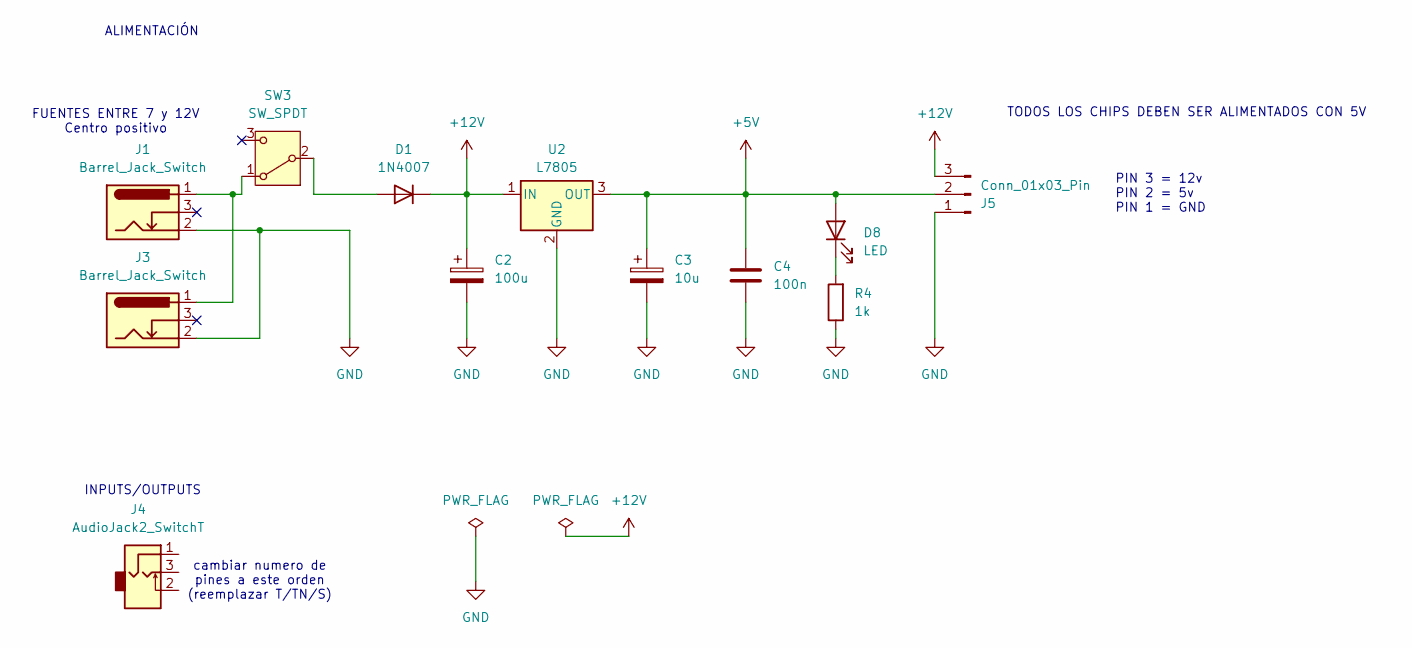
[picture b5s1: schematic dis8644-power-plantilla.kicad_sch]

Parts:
C2: 100u; CP_Radial_D8.0mm_P3.80mm
C3: 10u; CP_Radial_D4.0mm_P2.00mm
C4: 100n; C_Disc_D5.0mm_W2.5mm_P2.50mm
D1: 1N4007; D_DO-41_SOD81_P10.16mm_Horizontal
D8: LED; LED_D5.0mm
J1, J3: Barrel_Jack_Switch; BarrelJack_Horizontal
J4: AudioJack2_SwitchT; PJ301M-12
J5: Conn_01x03_Pin; PinSocket_1x03_P2.54mm_Vertical
R4: 1k; R_Axial_DIN0207_L6.3mm_D2.5mm_P10.16mm_Horizontal
SW3: SW_SPDT; spdt_ssd12d00g3
U2: L7805; TO-220-3_Horizontal_TabDown

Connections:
+5V: C3.1, C4.1, D8.2 (A), J5.2, U2.3 (OUT); also elsewhere on the board
+12V: C2.1, D1.1 (K), J5.3, U2.1 (IN)
GND: C2.2, C3.2, C4.2, J1.2, J3.2, J5.1, R4.1, U2.2 (GND); also elsewhere on the board
unnamed: D1.2 (A), SW3.2 (B)
unnamed: D8.1 (K), R4.2
unnamed: J1.1, J3.1, SW3.1 (A)

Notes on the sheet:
ALIMENTACIÓN
PIN 3 = 12v PIN 2 = 5v PIN 1 = GND
FUENTES ENTRE 7 y 12V Centro positivo
TODOS LOS CHIPS DEBEN SER ALIMENTADOS CON 5V
INPUTS/OUTPUTS
cambiar numero de pines a este orden (reemplazar T/TN/S)

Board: 2 copper layers, 13 parts (0 on the bottom side), 6 nets, no tracks yet.

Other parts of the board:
J2: Conn_01x02_Pin; PinHeader_2x01_P2.54mm_Vertical

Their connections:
+5V: J2.2; also elsewhere on the board
GND: J2.1; also elsewhere on the board

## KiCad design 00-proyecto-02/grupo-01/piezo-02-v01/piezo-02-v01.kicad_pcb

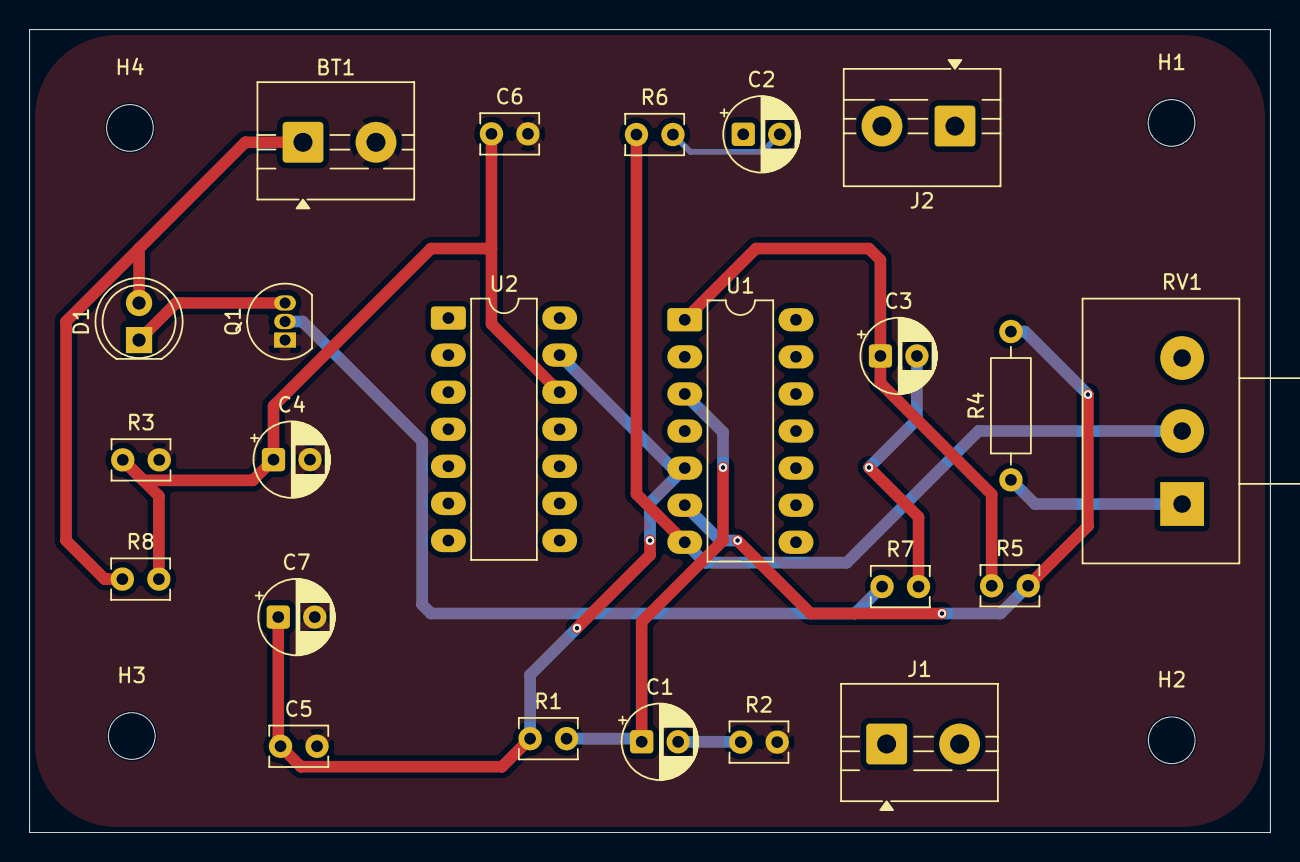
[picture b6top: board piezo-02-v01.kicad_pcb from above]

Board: 2 copper layers, 85.0 x 55.0 mm, 27 parts (0 on the bottom side), 14 nets.

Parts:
BT1: Battery_Cell; TerminalBlock_MaiXu_MX126-5.0-02P_1x02_P5.00mm
C1, C2: 1u; CP_Radial_D5.0mm_P2.50mm
C3, C4, C7: 10u; CP_Radial_D5.0mm_P2.50mm
C5, C6: 100n; C_Disc_D3.8mm_W2.6mm_P2.50mm
D1: LED; LED_D5.0mm
H1, H2, H3, H4: MountingHole; MountingHole_3.2mm_M3
J1, J2: TTS; TerminalBlock_MaiXu_MX126-5.0-02P_1x02_P5.00mm
Q1: PN2222A; TO-92_Inline
R1, R3, R8: 100k; C_Disc_D3.8mm_W2.6mm_P2.50mm
R2: 3M; C_Disc_D3.8mm_W2.6mm_P2.50mm
R4: 1k; R_Axial_DIN0207_L6.3mm_D2.5mm_P10.16mm_Horizontal
R5: 10k; C_Disc_D3.8mm_W2.6mm_P2.50mm
R6: 1k; C_Disc_D3.8mm_W2.6mm_P2.50mm
R7: 22k; C_Disc_D3.8mm_W2.6mm_P2.50mm
RV1: 500k; Potentiometer_Alps_RK163_Single_Horizontal
U1, U2: LM324; DIP-14_W7.62mm_LongPads

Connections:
GND: BT1.2 (-), C4.2, C5.2, C6.2, C7.2, Q1.1 (E), R2.2, R3.2
unnamed: C1.2, R2.1
unnamed: C2.2, R6.2
unnamed: C3.2, R7.2
unnamed: D1.1 (K), Q1.3 (C)
unnamed: Q1.2 (B), R7.1
unnamed: R4.1, RV1.1
unnamed: R6.1, RV1.2, U1.7
unnamed: C1.1, R1.2, U1.3 (+)
unnamed: C3.1, R5.1, U1.1, U1.2 (-)
unnamed: R4.2, R5.2, U1.6 (-)
unnamed: C4.1, C6.1, R3.1, R8.2, U2.12 (+)
VBUS: C5.1, C7.1, R1.1, U1.5 (+), U2.13 (-), U2.14
VCC: BT1.1 (+), D1.2 (A), R8.1
